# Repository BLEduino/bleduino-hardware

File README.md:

BLEduino Hardware
=================
Here you'll find all of the hardware design files related to the BLEduino and Shield-Shield.

* Bill of Materials - The full parts list used on the BLEduino and the Shield-Shield.
* Eagle - Schematic and PCB files for the BLEduino and Shield-Shield.
* Gerber - All of the Gerber files needed to produce your own BLEduinos or Shield-Shield.
* PDFs - PDF copies of the schematics and pcb including the individual layers.

These files are licensed under a [Creative Commons Attribution Share-Alike license](http://creativecommons.org/licenses/by-sa/2.5/).  That means you're allowed to modify, view, distribute, and remix any of the files for personal and comerical purposes as long as you credit the BLEduino and release your design files under the same or similar license.

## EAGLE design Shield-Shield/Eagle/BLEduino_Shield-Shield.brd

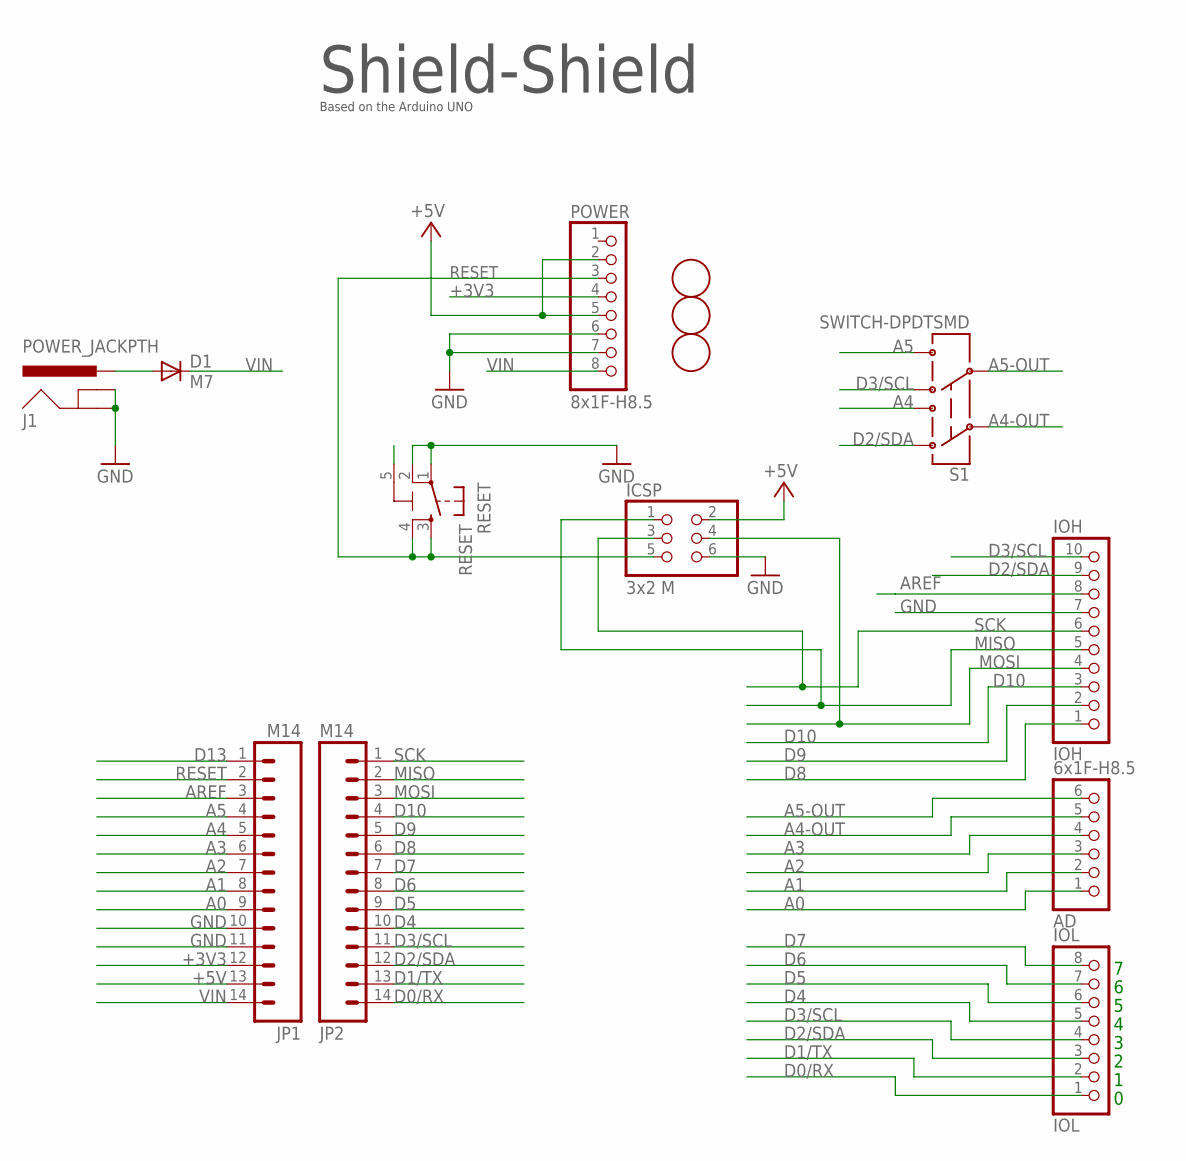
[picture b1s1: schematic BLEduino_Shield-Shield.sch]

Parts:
AD: 6x1F-H8.5; 1X06
D1: M7; SMB
FD1, FD2, FD3: FIDUCIALMOUNT; FIDUCIA-MOUNT
ICSP: 3x2 M; 2X03
IOH: IOH; 1X10
IOL: IOL; 1X08
J1: POWER_JACKPTH; POWER_JACK_PTH
JP1, JP2: M14; 1X14
POWER: 8x1F-H8.5; 1X08
RESET: RESET; TS42
S1: SWITCH-DPDTSMD; AYZ0202

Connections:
+3V3: JP1.12, POWER.4
+5V: ICSP.2, JP1.13, POWER.2, POWER.5
A0: AD.1, JP1.9
A1: AD.2, JP1.8
A2: AD.3, JP1.7
A3: AD.4, JP1.6
A4: JP1.5, S1.3
A4-OUT: AD.5, S1.2
A5: JP1.4, S1.6
A5-OUT: AD.6, S1.5
AREF: IOH.8, JP1.3
D0/RX: IOL.1, JP2.14
D1/TX: IOL.2, JP2.13
D2/SDA: IOH.9, IOL.3, JP2.12, S1.1
D3/SCL: IOH.10, IOL.4, JP2.11, S1.4
D4: IOL.5, JP2.10
D5: IOL.6, JP2.9
D6: IOL.7, JP2.8
D7: IOL.8, JP2.7
D8: IOH.1, JP2.6
D9: IOH.2, JP2.5
D10: IOH.3, JP2.4
D13: JP1.1
GND: ICSP.6, IOH.7, J1.GND, J1.GNDBREAK, JP1.10, JP1.11, POWER.6, POWER.7, RESET.1, RESET.2
MISO: ICSP.1, IOH.5, JP2.2
MOSI: ICSP.4, IOH.4, JP2.3
unnamed: D1.A, J1.PWR
RESET: ICSP.5, JP1.2, POWER.3, RESET.3, RESET.4
SCK: ICSP.3, IOH.6, JP2.1
VIN: D1.C, JP1.14, POWER.8

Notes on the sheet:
Shield-Shield
Based on the Arduino UNO

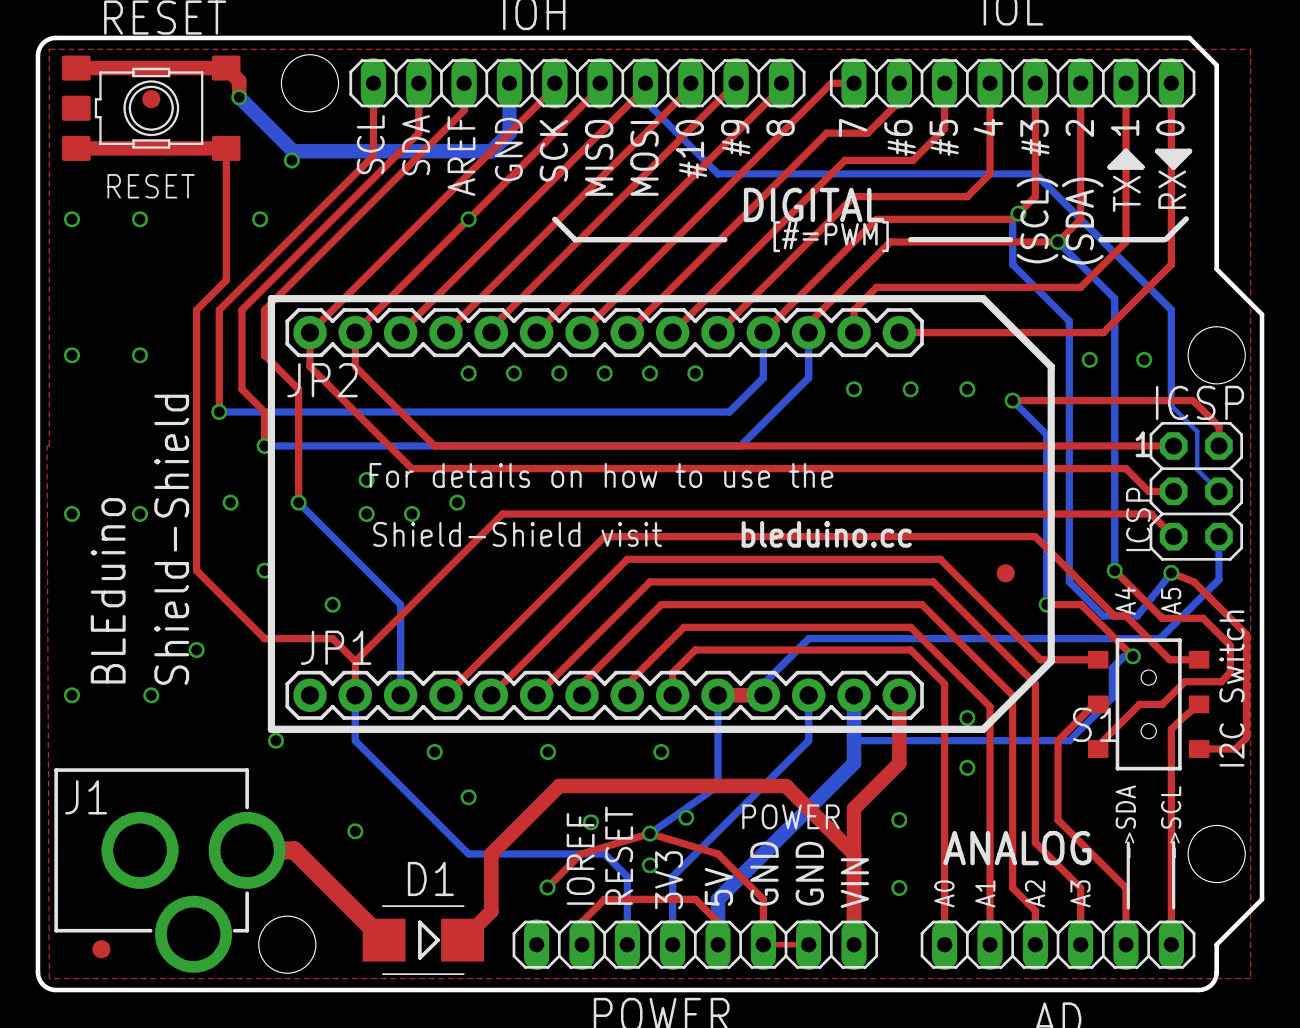
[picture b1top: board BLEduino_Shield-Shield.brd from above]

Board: 4 copper layers, 68.6 x 53.3 mm, 15 parts (1 on the bottom side), 29 nets.

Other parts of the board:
U$1: KYTELABS_LOGO_BIG

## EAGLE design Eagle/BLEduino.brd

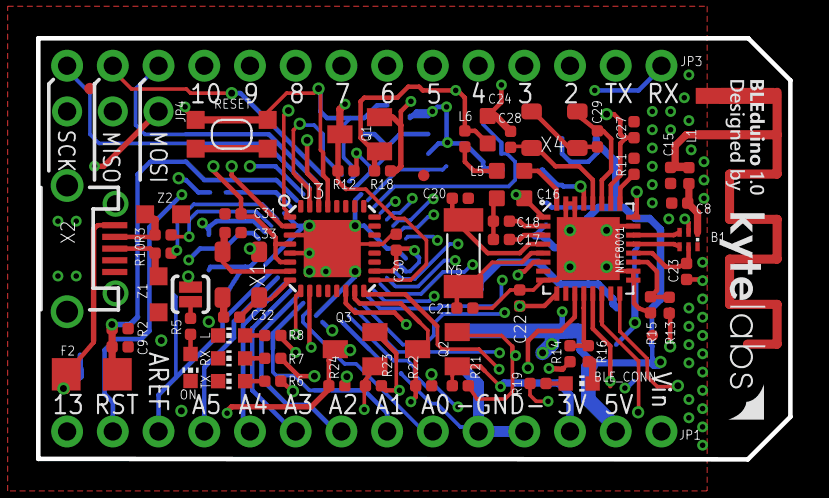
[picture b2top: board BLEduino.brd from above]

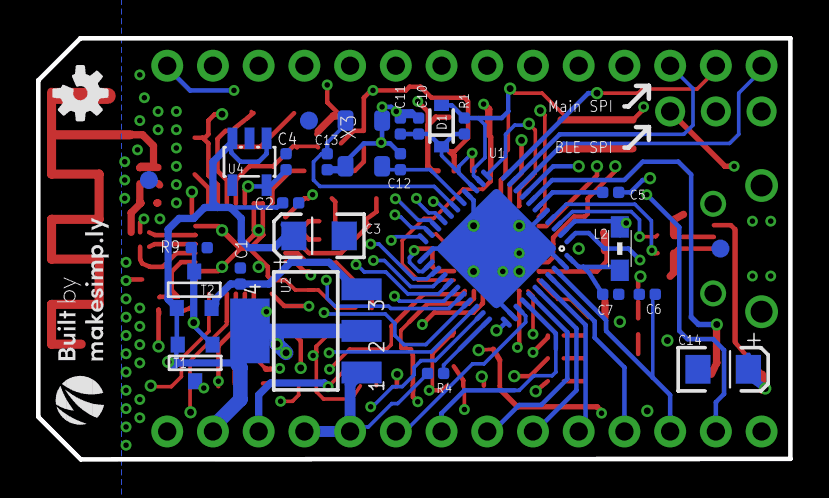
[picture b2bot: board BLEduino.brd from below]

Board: 6 copper layers, 41.8 x 23.4 mm, 96 parts (27 on the bottom side), 78 nets.

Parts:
ANT1: ANTENNA; RN-ANT
B1: BALUN0603; BALUN-0603
BLE_CONN: blue; CHIP-LED0603
C1, C2, C6, C9, C10, C11, C30, C31: 100n; C0402
C3, C14: 22u; EIA3216
C4, C5, C7: 1uF; C0402
C8, C15: n/a; C0402
C12, C13: 22pF; C0402
C16, C24: 1uF; C0603
C17: 33nF; C0402
C18, C22: 100nF; C0402
C20, C21, C28, C29: 15pF; C0402
C23: 2.2nF; C0402
C27: 1nF; C0402
C32, C33: 22p; C0402
D1: SOD-323
F2: R1206
JP1, JP3: 1X14-CB
JP2, JP5, JP6: FIDUCIALUFIDUCIAL; MICRO-FIDUCIAL
JP4: 1X03-CLEANBIG
L: yellow; CHIP-LED0603
L1: n/a; L0402
L2: MH2029-300Y; 0805
L5: 10uH; L0603
L6: 15nH; L0402
LOGO_BOTTOM: OSHW-LOGO-S
LOGO_TOP: V3_KYTELABS_TOP
NRF8001: FITNESSDEVICE_NRF8001; FITNESSDEVICE_QFN-32
ON: green; CHIP-LED0603
Q1, Q2, Q3: BSS138; SOT23
R1, R2, R4, R9, R12, R13, R14, R18, R21, R22, R23, R24: 10K; R0402
R3, R10: 22; R0402
R5, R6, R7, R8, R19: 1K; R0402
R11: 22K; R0402
R15, R16: 20K; R0402
RESET: SPST_TACT-KMR2; KMR2
RX: yellow; CHIP-LED0603
SILK_2: V3_MAKESIMPLY_BOTTOM
SJ1: SOLDERJUMPERNC2; SJ_2S-NOTRACE
T1: FDN340P/PMV48XP; SOT-23
T2: PMV48XP; SOT-23
TX: yellow; CHIP-LED0603
U1: ATMEGA32U4-XUMU; QFN44ML7X7
U2: NCP1117-5; LINEAR_SOT223
U3: ATMEGA8/168/328MLF; MLF32X-W/HEAT
U4: LP2985-33DBVR; SOT23-DBV
U$28, U$29, U$53: FIDUCIAL1X2; FIDUCIAL-1X2
X1, X3, X4: 4P-SMD-3.2X2.5
X2: SPARKFUN_USB-MICROB
Y5: Y5; FITNESSDEVICE_CRYSTAL-ABS10
Z1, Z2: CG0603MLC-05E; CT/CN0603

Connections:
3V3: C4.1, C16.1, C22.2, C24.1, C27.1, JP1.12, L6.2, NRF8001.1, NRF8001.9, NRF8001.24, NRF8001.26, NRF8001.29, Q1.1, Q2.1, Q3.1, R18.2, R21.2, R23.2, U4.5
+5V: C2.1, C3.A, C10.1, C11.1, C30.1, C31.1, D1.1, JP1.13, L2.1, R1.1, R12.1, R22.1, R24.1, SJ1.1, T1.2, T2.3, U1.2, U1.14, U1.24, U1.34, U2.2, U2.4, U3.4, U3.6, U3.18, U4.1, U4.3
+VIN: C1.1, T2.2, U2.3
A0: JP1.9, U1.36
A1: JP1.8, U1.37
A2: JP1.7, U1.38
A3: JP1.6, U1.39
A4: JP1.5, U1.40
A5: JP1.4, U1.41
AREF: C6.1, JP1.3, U1.42
AVCC: C7.1, L2.2, U1.44
BLE_ACTIVE: NRF8001.6, U3.9
BLE_MISO: JP4.2, Q3.3, R24.2, U3.16
BLE_MISO_SHIFTED: NRF8001.14, Q3.2, R23.1
BLE_MOSI: JP4.3, Q2.3, R22.2, U3.15
BLE_MOSI_SHIFTED: NRF8001.13, Q2.2, R21.1
BLE_RDNY: NRF8001.16, U3.1
BLE_REQN: R14.1, U3.14
BLE_REQN_SHIFTED: NRF8001.12, R14.2, R16.2
BLE_RESET: R13.1, U3.2
BLE_RESET_SHIFTED: NRF8001.19, R13.2, R15.2
BLE_SCK: JP4.1, Q1.3, R12.2, U3.17
BLE_SCK_SHIFTED: NRF8001.11, Q1.2, R18.1
D0/RX: JP3.14, U1.20
D1/TX: JP3.13, U1.21
D2/SDA: JP3.12, U1.19
D3/SCL: JP3.11, U1.18
D4*: JP3.10, U1.25
D5*: JP3.9, U1.31
D6*: JP3.8, U1.27
D7: JP3.7, U1.1
D+: R10.2, X2.D+, Z1.1
D-: R3.2, X2.D-, Z2.1
GND: ANT1.GND, B1.2, BLE_CONN.C, C1.2, C2.2, C3.C, C4.2, C5.2, C6.2, C7.2, C8.2, C9.2, C10.2, C11.2, C12.1, C13.1, C14.C, C15.2, C16.2, C17.2, C18.2, C20.2, C21.2, C22.1, C23.1, C24.2, C27.2, C28.2, C29.2, C30.2, C31.2, C32.2, C33.2, JP1.10, JP1.11, L.C, NRF8001.8, NRF8001.17, NRF8001.18, NRF8001.23, NRF8001.30, NRF8001.31, NRF8001.EP, ON.C, R2.1, R4.2, R9.1, R11.2, R15.1, R16.1, RESET.2, RESET.4, RX.C, TX.C, U1.5, U1.15, U1.23, U1.35, U1.43, U1.EXP, U2.1, U3.3, U3.5, U3.21, U3.HEAT, U4.2, X1.1, X1.3, X2.GND, X3.1, X3.3, X4.1, X4.3, Z1.2, Z2.2
HWB: R4.1, U1.33
IO8: JP3.6, U1.28
IO9*: JP3.5, U1.29
IO10*: JP3.4, U1.30
IO11*: U1.12, U3.31
IO12*: U1.26, U3.30
IO13*: JP1.1, R8.1, U1.32
MISO: JP3.2, U1.11
MOSI: JP3.3, U1.10
unnamed: C33.1, U3.7, X1.4
unnamed: R7.2, RX.A
unnamed: ON.A, R5.2
unnamed: R6.2, TX.A
unnamed: C32.1, U3.8, X1.2
unnamed: R19.2, U3.10
unnamed: L.A, R8.2
unnamed: BLE_CONN.A, R19.1
unnamed: ANT1.FEED, C15.1, L1.2
unnamed: C18.1, NRF8001.2
unnamed: R5.1, SJ1.2
unnamed: L5.1, NRF8001.32
unnamed: L5.2, L6.1
unnamed: C17.1, NRF8001.3
unnamed: C20.1, NRF8001.4, Y5.P$1
unnamed: C21.1, NRF8001.5, Y5.P$2
unnamed: B1.5, C23.2, NRF8001.20
unnamed: B1.3, NRF8001.22
unnamed: B1.4, NRF8001.21
unnamed: B1.1, C8.1, L1.1
unnamed: NRF8001.25, R11.1
unnamed: C28.1, NRF8001.28, X4.4
unnamed: C29.1, NRF8001.27, X4.2
RD_N: R3.1, U1.3
RD_P: R10.1, U1.4
RESET: D1.2, JP1.2, R1.2, RESET.1, RESET.3, U1.13, U3.29
RXLED/SS: R7.1, U1.8
SCK: JP3.1, U1.9
TXLED: R6.1, U1.22
UCAP: C5.1, U1.6
VIN: JP1.14, R9.2, T1.3, T2.1
VUSB: C9.1, F2.1, R2.2, T1.1, U1.7
VUSBD: C14.A, F2.2, X2.VBUS
XTAL1: C13.2, U1.17, X3.2
XTAL2: C12.2, U1.16, X3.4

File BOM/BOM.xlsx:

Part | Quantity | Description | Package | Pads | Mounting type | Vendor | Descriptor
3.3V Regulator | 1 | LP2985-33DBVR | SOT-23 | 5 | SMD | TI | U4
5V Regulator NCP1117-5 | 1 | NCP1117ST50T3G | SOT-223 | 4 | SMD | ON | U2
3x1 Male Headers | 1 |  | 0.1" | 0 | SMD |  | JP4
1x14 Male Headers | 2 |  | 0.1" | 0 | SMD |  | JP1, JP3
Anti-Static Varistor | 2 | CG0603MLC-05E | 0603 | 2 | SMD | Bourns Inc. | Z1, Z2
ATMega32u4 | 1 | ATMEGA32U4-MU | QFN-44 | 45 | SMD | Atmel | U1
ATMega328P | 1 | ATMEGA328P-MUR | QFN-32 | 33 | SMD | Atmel | U3
BLE Controller | 1 | NRF8001-R2Q32-T | QFN-32 | 33 | SMD | Nordic Semiconductor | NRF8001
BALUN | 1 | 2450BM14A0002T | 0603 (6 pin) | 6 | SMD | Johanson Technology | B1
CAP 100n Ceramic | 10 | 0.1UF 25V 0402 | 0402 | 2 | SMD |  | C1, C2, C6, C9, C10, C11, C18, C22, C30, C31
CAP 15pF Ceramic | 4 | 15PF 16V 0402 | 0402 | 2 | SMD |  | C20, C21, C28, C29
CAP 1nF Ceramic | 1 | 1000PF 10V 0402 | 0402 | 2 | SMD |  | C27
CAP 1u Ceramic | 3 | 1UF 16V 0402 | 0402 | 2 | SMD |  | C5, C4, C7
CAP 1uF Ceramic | 2 | 1UF 16V 0603 | 0603 | 2 | SMD |  | C16, C24
CAP 2.2nF Ceramic | 1 | 2200PF 25V 0402 | 0402 | 2 | SMD |  | C23
CAP 22p Ceramic | 4 | 22PF 16V 0402 | 0402 | 2 | SMD |  | C12, C13, C32, C33
CAP 22u Tantalum (Polarized) | 2 | CAP TANT 22UF 25V 1206 | 1206 | 2 | SMD |  | C3, C14
CAP 33nF Ceramic | 1 | 0.033UF 10V 0402 | 0402 | 2 | SMD |  | C17
CAP 2pF Ceramic | 1 | 2.0pF 10V 0402 | 0402 | 2 | SMD |  | C15
IND 10uH | 1 | 10UH 50mA 0402 | 0603 | 2 | SMD |  | L5
IND 15nH | 1 | 15NH 50mA 0402 | 0402 | 2 | SMD |  | L6
Crystal 16MHz | 3 | CRYSTAL 16MHZ 20PF SMD | 3.20mm x 2.50mm | 4 | SMD |  | Y2, Y3, Y4
Crystal 32,768KHz | 1 | CRYSTAL 32,768 KHZ 12.5PF SMD | 4.90mm x 1.80mm | 2 | SMD |  | Y5
Diode | 1 | DIODE 10V SOD-323 | SOD-323 | 2 | SMD |  | D1
Ferrite Bead | 1 | MH2029-300YCT | 0805 | 2 | SMD |  | L2
LED Blue | 1 | BLUE ~470NM DIFFUSED 0603 | 0603 | 2 | SMD |  | BLE_CONN
LED Green | 1 | GREEN ~570NM DIFFUSED 0603 | 0603 | 2 | SMD |  | ON
LED Yellow | 3 | YELLOW ~587NM DIFFUSED 0603 | 0603 | 2 | SMD |  | RX, TX, L
Level Converter BSS138 | 3 | BSS138-7-F | SOT-23 | 3 | SMD | Diodes Inc. | Q1, Q2, Q3
P-FET PMV48XP | 2 | PMV48XP,215 | SOT-23 | 3 | SMD | NXP | T1, T2
PTC | 1 | PTC 500mA | 1206 | 2 | SMD |  | F2
RES 10K | 11 | 10K J 1/10W 0402 | 0402 | 2 | SMD |  | R1, R2, R4, R9, R12, R13, R14, R18, R21, R22, R23, R24
RES 1K | 5 | 1K J 1/10 0402 | 0402 | 2 | SMD |  | R5, R6, R7, R8, R19
RES 20K | 1 | 20K J 1/10W 0402 | 0402 | 2 | SMD |  | R15, R16
RES 22 | 2 | 22R J 1/10W 0402 | 0402 | 2 | SMD |  | R3, R10
RES 22K | 1 | 22K J 1/8W 0402 | 0402 | 2 | SMD |  | R11
RES 0 |  | 0 Ohm resistor 0402 | 0402 | 2 | SMD |  | L1
Small Push Button | 1 | SWITCH TACTILE KMR2 |  | 4 | SMD |  | RESET
Micro USB Connector | 1 | 10118194-0001LF |  | SMD - 5 Through - 4 | SMD/Through-hole | FCI | X2

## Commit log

2013-09-30 First hardware source commit.
    All the hardware source files or the BLEduino. Needs a few minor
    changes.
2013-10-01 Added some missing info in the BOM
2013-10-01 Updated the README
2013-10-08 Antenna was missing, added it.
2013-11-02 Updated BOM
2013-11-02 Updated BOM with necessary manufacturing details
2013-11-16 Updated design files and BOM with the latest 6-layered board
2014-01-11 Final BLEduino Hardware Files
2014-01-11 Changed some file names.
2014-05-18 Latest BLEduino Files
    Should be the same as the BLEduino that will ship.
2014-08-20 BOM Update
    Fixed a few errors in the BOM and made it more readable. Also uploaded
    it in PDF for convenience.
2014-08-21 Merged BLEduino repository with Shield-Shield repository.
2014-10-24 Fixed BOM Crystal Labels
    Pointed out by forum user “christine_le”.

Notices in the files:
parts and their libraries:
Wuerth_Elektronik_eiSos_V6: Copyright: Würth Elektronik
SparkFun: Licensing: CC v3.0 Share-Alike You are welcome to use this library for commercial purposes.
